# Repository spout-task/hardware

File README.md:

# SPOUT hardware

Hardware for a **SPOUT** rig, part of the [spout-task](https://github.com/spout-task) project.
Every device has its own folder with design files, pictures and a README that explains what it does,
what to buy, how to make it and how to connect it to SPOUT.

A complete rig costs about **1,080 USD** (about 1,440 USD including a computer and screen).
The full bill of materials is in [`SPOUT_BOM.xlsx`](SPOUT_BOM.xlsx) and [`SPOUT_BOM.pdf`](SPOUT_BOM.pdf).

<p align="center"><em>A SPOUT rig seen from above: head restrained setup (left), motorized manipulator with the spouts (center), electronics with the Teensy breakout board (top), water reservoirs (top right) and the stepper motor driver box (right).</em></p>

## Devices

| Group | Device | What it does | How it is made | Folder |
|---|---|---|---|---|
| Electronics | Teensy breakout board | Carries the Teensy 4.1, drives the solenoids and brings out all inputs and outputs | PCB, 3D printed housing | [`teensy_breakout_board`](teensy_breakout_board/) |
| Electronics | Dual lick detector | Detects licks on one or two spouts with sub millisecond precision | PCB, 3D printed housing | [`dual_lick_detector`](dual_lick_detector/) |
| Electronics | Optogenetics power modulator | Turns a Teensy PWM signal into a 0 to 5 V analog command, so light power can be set per trial | Hand built circuit, 3D printed housing | [`optogenetics_power_modulator`](optogenetics_power_modulator/) |
| Head fixation | Head restrained setup | Headplates and holders for behavior and for two photon imaging | Laser cut titanium headplates, machined aluminium holders, ramps and cone | [`head-restrained_setup`](head-restrained_setup/) |
| Head fixation | Breadboards | Rig base plate and round base for the head fixation | Machined aluminium by a machine shop (or bought) | [`breadboards`](breadboards/) |
| Spout positioning | Motorized manipulator | Three axis stepper stage that positions the spouts | Bought stages and drivers, 3D printed adapters, laser cut driver box and drilling templates | [`motorized_manipulator`](motorized_manipulator/) |
| Spout positioning | Spout holder | Holds the stainless steel lick spout(s) and the two solenoid valves | 3D printed spout holders, laser cut solenoid holder | [`spout_holder`](spout_holder/) |
| Miscellaneous | Housings | Boxes for the audio amplifier and for the power distribution breadboard | 3D printed | [`housing_miscellaneous`](housing_miscellaneous/) |

## Build order for one rig

1. **Base.** The 12 x 18 inch breadboard is the base of the rig.
2. **Head fixation.** Build the head restrained setup on the round breadboard: magnetic base, post, clamp, aluminium tube and headplate holders.
3. **Water delivery.** Reservoir syringes, 3 way valves, solenoids in the solenoid holder, Tygon tubing, and the spouts in the spout holder.
4. **Spout positioning.** Stack the three linear stages with the printed adapters, mount the spout holder on a post on the top stage, and put the three drivers in the laser cut box.
5. **Electronics.** Teensy breakout board in its housing, power distribution box, dual lick detector in its housing. Connect the spouts to the lick detector and ground the mouse through the aluminium tube.
6. **Sound.** Audio amplifier in its housing and two speakers on short posts.
7. **Optogenetics (optional).** Optogenetics power modulator between the Teensy and the LED or AOM driver.
8. **Software.** Flash the firmware and open the GUI, see the [software](https://github.com/spout-task/software) repository.

Photos of the build process will be added.

## Conventions

* 3D printed parts: Prusa MK3, PLA, standard settings.
* Screws: 1/4 20 for the breadboards and posts, 4-40 for small parts.
* Units: mm, except the breadboard STEP files (inch). DXF files are in mm.
* Each device folder has a `design` folder with `files` (design files) and `pictures` (renders). Electronics also have a `PCB` or `circuit` folder, and the manipulator a `schematics` folder.
* File types: STL to 3D print, DXF to laser cut, STEP to edit in CAD or to send to a machine shop. Flat parts come as DXF and STL, so you can laser cut or print them.
* Each README lists for every part how we made it and from what material.

## Related repositories
[software](https://github.com/spout-task/software), [analyses](https://github.com/spout-task/analyses), [settings](https://github.com/spout-task/settings), [example_data](https://github.com/spout-task/example_data)

## License
All hardware designs in this repository are released under **CERN-OHL-S-2.0** ([`LICENSE`](LICENSE)).
The dual lick detector and the Teensy breakout board were designed by the
[HMS Research Instrumentation Core](https://github.com/HMS-RIC), whose members are authors of SPOUT,
and are shared here as part of SPOUT. Newer revisions are developed in the HMS RIC repositories for the
[lick detector](https://github.com/HMS-RIC/2-Channel-Lick-Detector) and the
[Teensy breakout board](https://github.com/HMS-RIC/Teensy-Breakout-general-purpose).

## How to cite
See [`CITATION.cff`](CITATION.cff) and the [project overview](https://github.com/spout-task).

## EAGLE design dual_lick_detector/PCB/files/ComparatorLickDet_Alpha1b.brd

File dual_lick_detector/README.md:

# Dual lick detector

Two channel lick detector for head restrained mice. Each lick closes a tiny current path between the
spout and the grounded mouse; the detector turns that into a clean digital pulse for the Teensy, with
sub millisecond precision.

## At a glance

| | |
|---|---|
| Function | Detects licks on one or two spouts |
| Design | HMS Research Instrumentation Core, revision Alpha1e (KiCad 10) |
| Fabrication | PCB with commercial assembly, 3D printed housing |
| Approximate cost | 100 USD for the assembled board |
| Used by | SPOUT1 (one channel) and SPOUT2 (two channels) |

## Key features

* Battery powered, optically isolated front end.
* Adjustable threshold and (optionally) adjustable hysteresis (100 mV default).
* Multi turn potentiometers for fine adjustment; can be fitted with a scale dial.
* Selectable conduction mode or junction potential mode. SPOUT uses conduction mode.
* Power from micro USB or a barrel jack adapter.
* Indicator LEDs for power and lick detection; ESD protected front end.
* Optional input protection diodes to support shock delivery.

## How it works in SPOUT

In conduction mode each spout is pulled up to 9 V (from a 9 V battery) through a 4.7 MOhm resistor.
When the grounded mouse touches the spout, the voltage drops and a comparator switches. The input is
filtered with a 10 us RC filter and the comparator has 100 mV hysteresis. An optically isolated output
stage, powered by a separate 3 V adapter, drives the output through a 50 Ohm source termination, so the
signal can run over BNC cables. In the SPOUT configuration the output is active low.

## Files

| File | What it is |
|---|---|
| [`PCB/files/dual_lick_detector_.kicad_sch`](PCB/files/dual_lick_detector_.kicad_sch) | Schematic (KiCad 10) |
| [`PCB/files/dual_lick_detector_.kicad_pcb`](PCB/files/dual_lick_detector_.kicad_pcb) | Board layout (KiCad 10) |
| [`ComparatorLickDet_BOM.pdf`](ComparatorLickDet_BOM.pdf) | Component list, readable version (made for revision Alpha1d) |
| [`PCB/pictures`](PCB/pictures/) | Photos and board renders, see below |

| Part | Files | What it is | How we made it |
|---|---|---|---|
| Housing | [`.stl`](design/files/box_dual_lick_detector.stl), [`.step`](design/files/box_dual_lick_detector.step) | Housing, 152 x 89 x 20 mm, with mounting ears | 3D printed, PLA |

The SPOUT paper used revision Alpha1d (EAGLE). Alpha1e is the KiCad version of that design.
Newer revisions are developed in the [HMS RIC repository](https://github.com/HMS-RIC/2-Channel-Lick-Detector).

### Pictures

| Picture | What it shows |
|---|---|
| [`dual_lick_detector_1.jpg`](PCB/pictures/dual_lick_detector_1.jpg) | Assembled board with BNC connectors, potentiometers and battery holder |
| [`dual_lick_detector_2.jpg`](PCB/pictures/dual_lick_detector_2.jpg) | Bare board, top |
| [`dual_lick_detector_3.jpg`](PCB/pictures/dual_lick_detector_3.jpg) | Bare board, bottom |
| [`dual_lick_detector_schematic_1.png`](PCB/pictures/dual_lick_detector_schematic_1.png) | Board render from KiCad, bottom |
| [`dual_lick_detector_schematic_2.png`](PCB/pictures/dual_lick_detector_schematic_2.png) | Board render from KiCad, top |

## Bill of materials

| Qty | Part | Supplier | Part number | Price (USD) |
|---|---|---|---|---|
| 1 | Assembled lick detector board | Any PCB assembler (we used PCBWay) | KiCad files | 100 |
| 1 | 3D printed housing | | | |
| 1 | 9 V battery | | | |
| 1 | Power adapter 3 V (output stage) | NC | BY0301&BK | 5.57 |
| 1 | Stainless steel tube for the spouts | McMaster-Carr | 5560K72 | 3.90 |
| 1 | Banana socket and plug (mouse ground) | | | 2.98 |

Full list: [`SPOUT_BOM.xlsx`](../SPOUT_BOM.xlsx).

## Ordering the PCB

The board is designed in KiCad 10. Open the `.kicad_pcb` file in KiCad (free, [kicad.org](https://www.kicad.org)) and export
what your fabricator needs: Gerber and drill files (File, Fabrication Outputs), and for commercial assembly the
component list and the position file from the same menu. Default manufacturing settings are fine.

## Fabrication

1. Order the assembled board as described above. All the fine soldering will be done, you only need to solder big components on the PCB. The SPOUT boards were made and assembled by PCBWay.
2. On both sides of the PCB, solder dual jack BNC connectors in place.
3. On the top side of the PCB, you will have to solder two multi-turn potentiometers in place.
4. On the bottom side of the PCB, a DC barrel jack power connector (3V to send TTL to Teensy) and/or micro USB connector (5V if you want to send a TTL to an Arduino), a two-way toggle switch, and a 9V battery casing should be soldered in place.
5. Print `box_dual_lick_detector.stl` on a Prusa MK3 in PLA with standard settings. Mount the board with 4-40 screws and the housing on the breadboard with 1/4 20 screws.

## Assembly

1. Mount the board in the housing and the housing on the breadboard.
2. Connect the spouts to the inputs, and the outputs to the Teensy breakout board, as listed below.
3. Ground the mouse: connect the detector ground to the aluminium tube of the head restrained setup with the banana plug and socket.
4. Insert the 9 V battery and connect the 3 V adapter.
5. For imaging, split the lick outputs with a BNC T connector to your DAQ as well.

## Connections

Seen from the top, with the potentiometers facing up. Each side has two BNC connectors, one above the other.

| Part | SPOUT2 (two spouts) | SPOUT1 (one spout) |
|---|---|---|
| Left BNC, top | Left lick output, to PIN14_A0 on the Teensy breakout board | Lick output, to PIN14_A0 |
| Left BNC, bottom | Right lick output, to PIN41_A17 | Not used |
| Right BNC, top | Left lick input, from the left spout | Lick input, from the spout |
| Right BNC, bottom | Right lick input, from the right spout | Not used |
| Bottom LED | Left lick detected | Lick detected |
| Top LED | Right lick detected | Not used |
| Left potentiometer | Left lick threshold | Lick threshold |
| Right potentiometer | Right lick threshold | Not used |

## Testing and calibration

1. Touch a spout with one hand while touching the ground (aluminium tube) with the other: the lick LED lights up and the GUI shows the lick.
2. Set the threshold with the multi turn potentiometer (left for the left spout, right for the right spout) so a touch is detected reliably while the idle spout stays silent. Set it per rig, because cable length and grounding differ.

## License and attribution
Designed and developed by the [HMS Research Instrumentation Core](https://github.com/HMS-RIC), whose
members are authors of SPOUT, and shared here as part of SPOUT under **CERN-OHL-S-2.0**
([`LICENSE`](../LICENSE)). Newer revisions are developed in the
[HMS RIC repository](https://github.com/HMS-RIC/2-Channel-Lick-Detector).

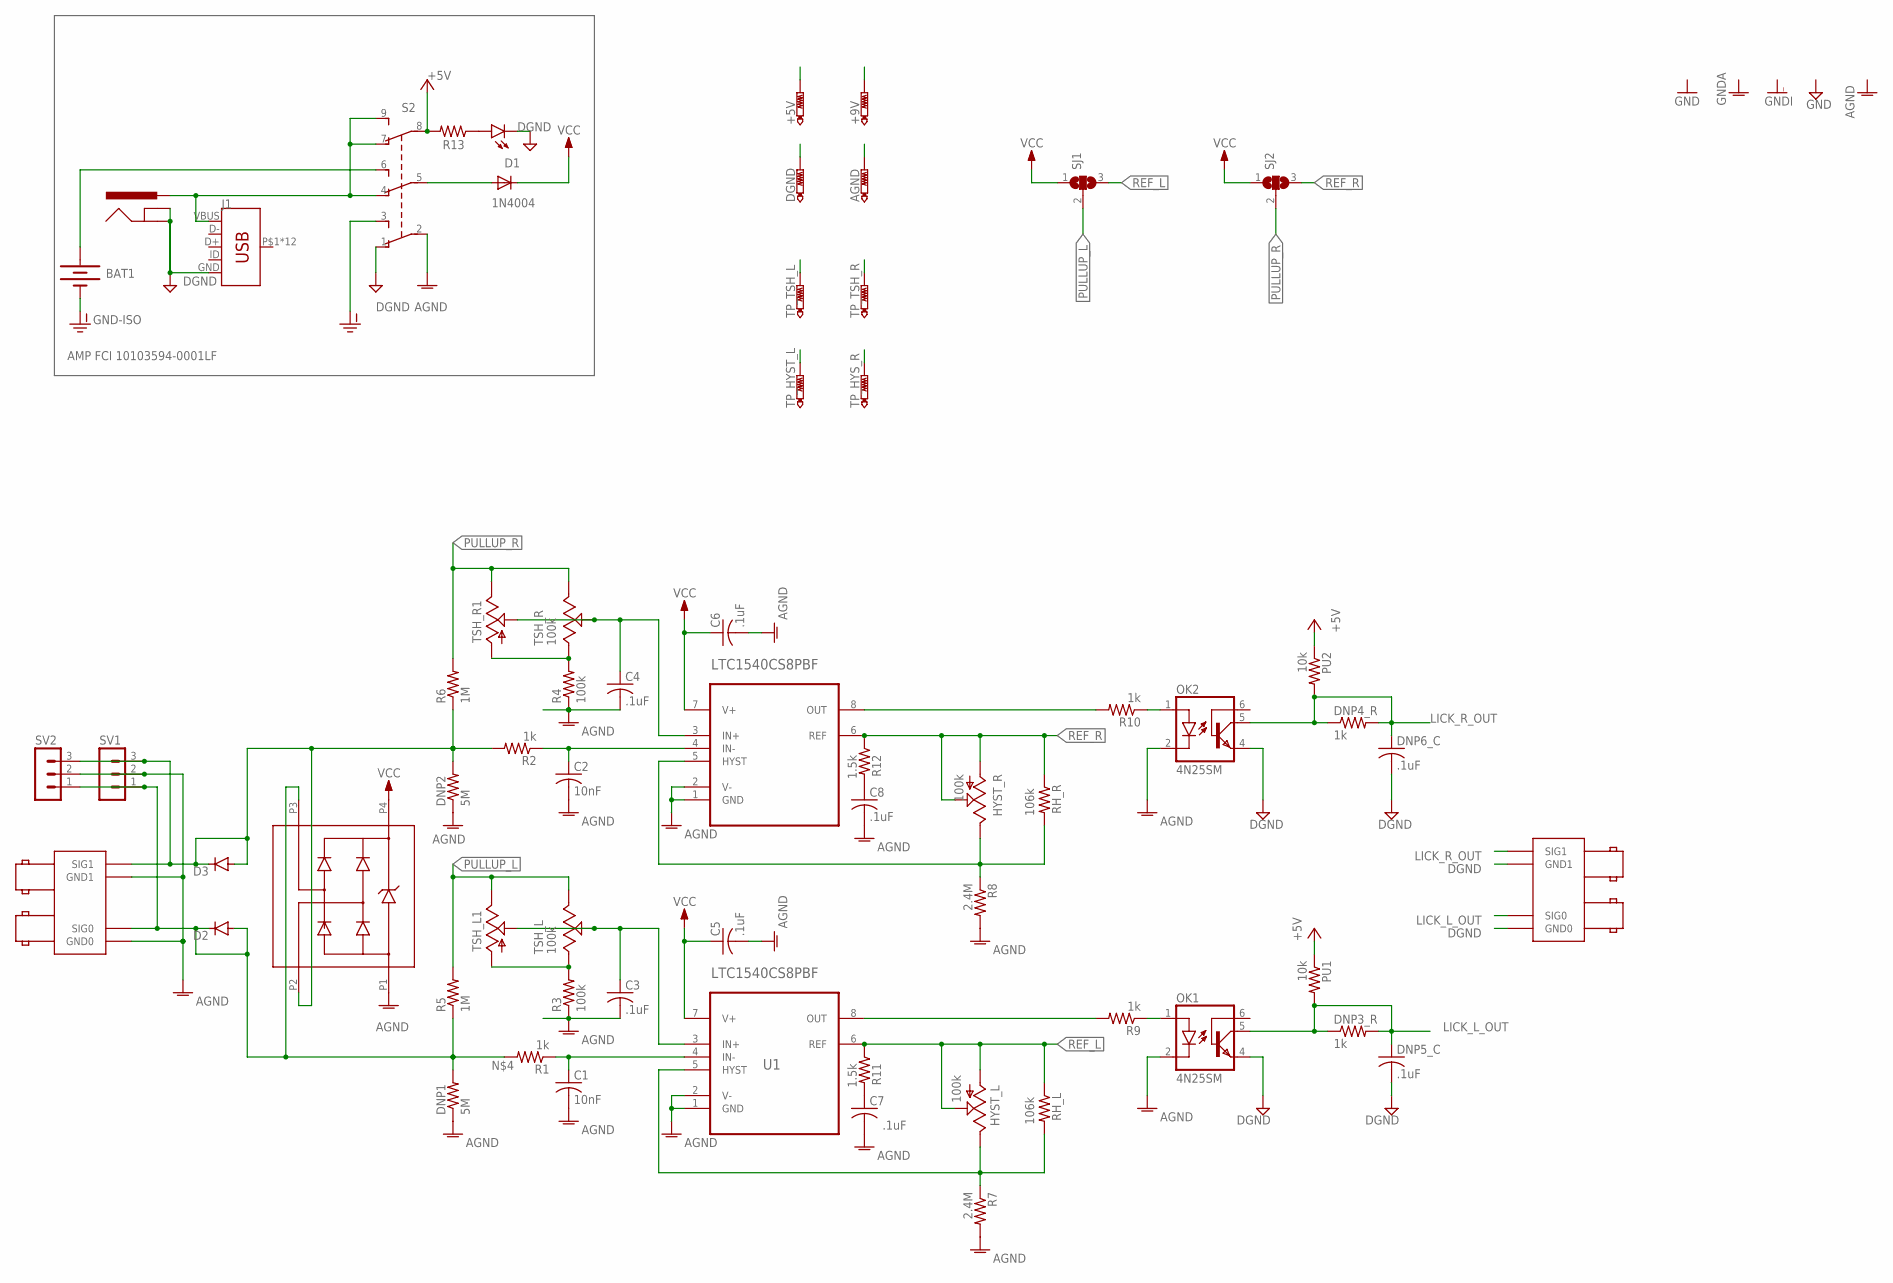
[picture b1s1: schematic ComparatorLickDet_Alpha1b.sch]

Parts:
+5V, +9V: PTR1PAD1-13Y; P1-13Y
AGND: PTR1PAD1-13Y; P1-13Y
BAT1: BATTERY9V; BATTCON_9V
C1, C2: 10nF; C0805
C3, C4, C5, C6, C7, C8: .1uF; C0805
D1: 1N4004; DO41-10
D2, D3: DIODE-D-2.5; D-2.5
DGND: PTR1PAD1-13Y; P1-13Y
DNP1, DNP2: 5M; M0805
DNP3_R, DNP4_R: 1k; M0805
DNP5_C, DNP6_C: .1uF; C0805
HYST_L: 100k; B25P
HYST_R: 100k; B25P
J1: AMP FCI 10103594-0001LF; USB-MICROB-PTH
JP10: POWER_JACKPTH_BREAD; POWER_JACK_PTH_BREAD
LICKS_IN: BNC_RIGHT_ANGLE_DOUBLE
LICKS_OUT: BNC_RIGHT_ANGLE_DOUBLE
OK1, OK2: 4N25SM; DIL6-SMD
PU1, PU2: 10k; M0805
PWR: LED3MM
R1, R2, R9, R10: 1k; M0805
R3, R4: 100k; M0805
R5, R6: 1M; M0805
R7, R8: 2.4M; M0805
R11, R12: 1.5k; M0805
R13: 330; R0805
RH_L: 106k; M0805
RH_R: 106k; M0805
S2: SWITCH-3PDT-TH-V; NKK-M20-9PIN-VERTICAL
SJ1, SJ2: SJ2W; SJ_2
SV1, SV2: MA03-1
TP_HYST_L: PTR1PAD1-13; P1-13
TP_HYS_R: PTR1PAD1-13; P1-13
TP_TSH_L: PTR1PAD1-13; P1-13
TP_TSH_R: PTR1PAD1-13; P1-13
TSH_L: 100k; TRIM_3590S-2-103L
TSH_L1: 100k; B25P
TSH_R: 100k; TRIM_3590S-2-103L
TSH_R1: 100k; B25P
U1, U2: LTC1540CS8PBF; SOIC127P600X175-8N
U3: CD143A-12_TVS; SOT-143

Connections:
+5V: +5V.TP, PU1.1, PU2.1, R13.2, S2.8 (P3)
+9V: +9V.TP, BAT1.+, S2.6 (S2)
AGND: AGND.TP, C1.2, C2.2, C3.2, C4.2, C5.2, C6.2, C7.2, C8.2, DNP1.1, DNP2.1, LICKS_IN.P$GND0 (GND0), LICKS_IN.P$GND1 (GND1), OK1.2 (C), OK2.2 (C), R3.1, R4.1, R7.2, R8.2, S2.2 (P1), SV1.2, SV2.2, U1.1 (GND), U1.2 (V-), U2.1 (GND), U2.2 (V-), U3.P1
DGND: DGND.TP, DNP5_C.2, DNP6_C.2, J1.GND, JP10.GND, JP10.GNDBREAK, LICKS_OUT.P$GND0 (GND0), LICKS_OUT.P$GND1 (GND1), OK1.4 (EMI), OK2.4 (EMI), PWR.K (C), S2.1 (O1)
GND-ISO: BAT1.-, S2.3 (S1)
HYST_L: HYST_L.E, R7.1, RH_L.2, TP_HYST_L.TP, U1.5 (HYST)
HYST_R: HYST_R.E, R8.1, RH_R.2, TP_HYS_R.TP, U2.5 (HYST)
LICK_L_IN: C1.1, R1.1, U1.4 (IN-)
LICK_L_OUT: DNP3_R.1, DNP3_R.2, DNP5_C.1, LICKS_OUT.P$SIG0 (SIG0), OK1.5 (COL), PU1.2
LICK_R_OUT: DNP4_R.1, DNP4_R.2, DNP6_C.1, LICKS_OUT.P$SIG1 (SIG1), OK2.5 (COL), PU2.2
unnamed: R3.2, TSH_L.1 (CCW), TSH_L1.A
unnamed: D2.A, D2.C, DNP1.2, LICKS_IN.P$SIG0 (SIG0), R1.2, R5.1, SV1.1, SV2.1, U3.P3
unnamed: J1.VBUS, JP10.PWR, S2.4 (O2), S2.7 (O3), S2.9 (S3)
unnamed: C7.1, R11.2
unnamed: R4.2, TSH_R.1 (CCW), TSH_R1.A
unnamed: C2.1, R2.1, U2.4 (IN-)
unnamed: C8.1, R12.2
unnamed: D3.A, D3.C, DNP2.2, LICKS_IN.P$SIG1 (SIG1), R2.2, R6.1, SV1.3, SV2.3, U3.P2
unnamed: PWR.A, R13.1
unnamed: OK1.1 (A), R9.1
unnamed: R9.2, U1.8 (OUT)
unnamed: OK2.1 (A), R10.1
unnamed: R10.2, U2.8 (OUT)
PULLUP_L: R5.2, SJ1.2, TSH_L.3 (CW), TSH_L1.E
PULLUP_R: R6.2, SJ2.2, TSH_R.3 (CW), TSH_R1.E
REF_L: HYST_L.A, HYST_L.S, R11.1, RH_L.1, SJ1.3, U1.6 (REF)
REF_R: HYST_R.A, HYST_R.S, R12.1, RH_R.1, SJ2.3, U2.6 (REF)
TSH_L: C3.1, TP_TSH_L.TP, TSH_L.2 (WIPER), TSH_L1.S, U1.3 (IN+)
TSH_R: C4.1, TP_TSH_R.TP, TSH_R.2 (WIPER), TSH_R1.S, U2.3 (IN+)
VCC: C5.1, C6.1, D1.C, SJ1.1, SJ2.1, U1.7 (V+), U2.7 (V+), U3.P4
VIN: D1.A, S2.5 (P2)

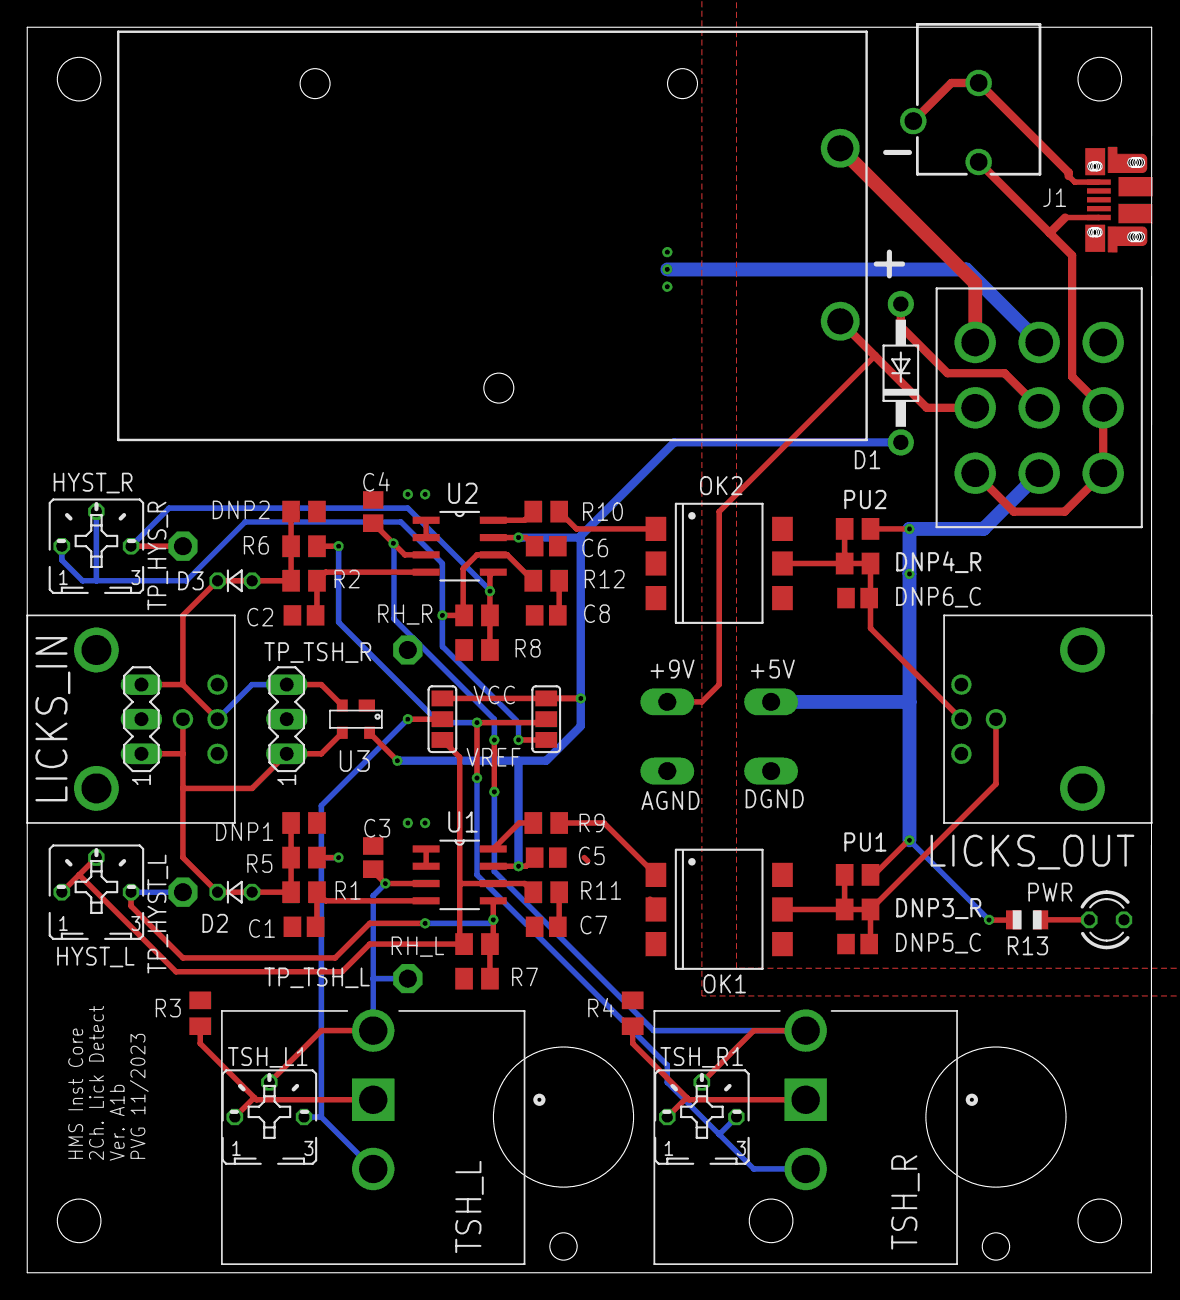
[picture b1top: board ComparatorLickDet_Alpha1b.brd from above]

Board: 2 copper layers, 82.5 x 91.4 mm, 64 parts (0 on the bottom side), 31 nets.

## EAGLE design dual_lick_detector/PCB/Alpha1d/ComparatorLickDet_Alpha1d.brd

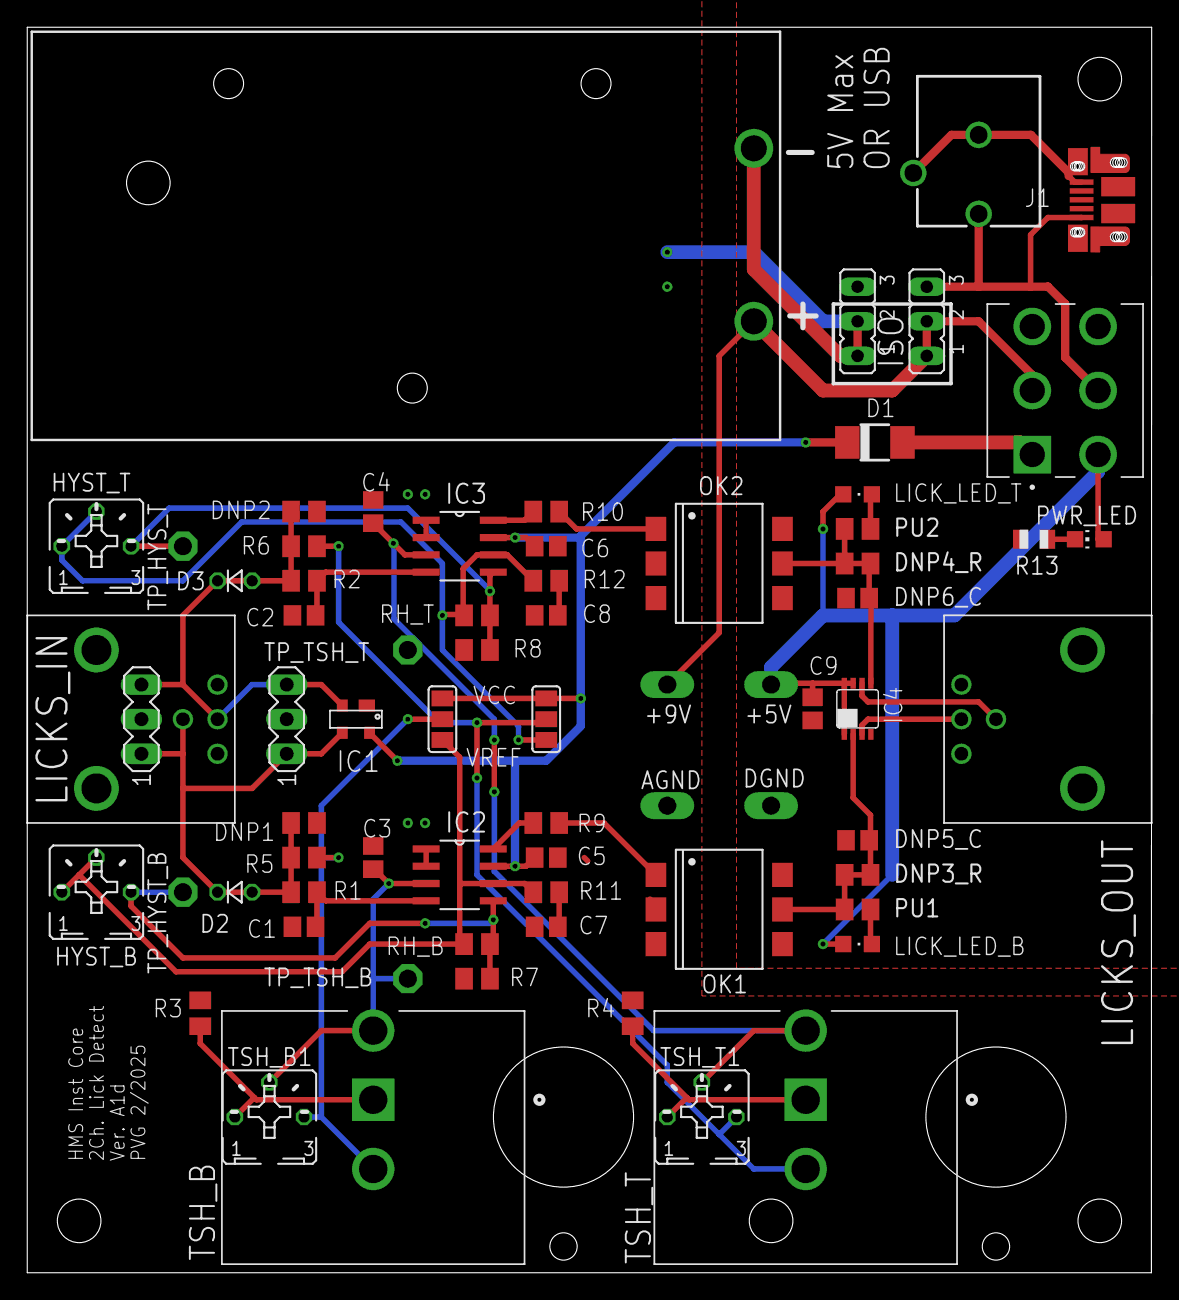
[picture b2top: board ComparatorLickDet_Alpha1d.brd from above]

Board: 2 copper layers, 82.5 x 91.4 mm, 70 parts (0 on the bottom side), 34 nets.

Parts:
+5V, +9V: PTR1PAD1-13Y; P1-13Y
AGND: PTR1PAD1-13Y; P1-13Y
BAT1: BATTCON_9V
C1, C2: 10nF; C0805
C3, C4, C5, C6, C7, C8, C9: .1uF; C0805
D1: DO-214AC
D2, D3: D-2.5
DGND: PTR1PAD1-13Y; P1-13Y
DNP1, DNP2: 5M; M0805
DNP3_R, DNP4_R: 1k; M0805
DNP5_C, DNP6_C: .1uF; C0805
HYST_B: 100k; B25P
HYST_T: 100k; B25P
IC1: CD143A-12_TVS; SOT-143
IC2, IC3: LTC1540CS8PBF; SOIC127P600X175-8N
IC4: SN74LVC2G126DCT; DCT_R-PDSO-G8
J1: AMP FCI 10103594-0001LF; USB-MICROB-PTH
JP1, JP2: JP2
JP10: POWER_JACKPTH_BREAD; POWER_JACK_PTH_BREAD
LICKS_IN: BNC_RIGHT_ANGLE_DOUBLE
LICKS_OUT: BNC_RIGHT_ANGLE_DOUBLE
LICK_LED_B: CHIPLED_0805
LICK_LED_T: CHIPLED_0805
OK1, OK2: 4N25SM; DIL6-SMD
PU1, PU2: 10k; M0805
PWR_LED: CHIP-LED0805
R1, R2, R9, R10: 1k; M0805
R3, R4: 51k; M0805
R5, R6: 4.7M; M0805
R7, R8: 2.4M; M0805
R11, R12: 1.5k; M0805
R13: 1k; R0805
RH_B: 100k; M0805
RH_T: 100k; M0805
S1: 500SDP1S1M2QEA; SW_500SDP1S1M2QEA
SJ1, SJ2: SJ_2
SV1, SV2: MA03-1
TP_HYST_B: PTR1PAD1-13; P1-13
TP_HYS_T: PTR1PAD1-13; P1-13
TP_TSH_B: PTR1PAD1-13; P1-13
TP_TSH_T: PTR1PAD1-13; P1-13
TSH_B: 100k; TRIM_3590S-2-103L
TSH_B1: 100k; B25P
TSH_T: 100k; TRIM_3590S-2-103L
TSH_T1: 100k; B25P

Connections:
+5V: +5V.TP, C9.1, IC4.1, IC4.7, IC4.8, LICK_LED_B.A, LICK_LED_T.A, PWR_LED.A, S1.4
+9V: +9V.TP, BAT1.+, JP1.1, JP1.2, S1.2
AGND: AGND.TP, BAT1.-, C1.2, C2.2, C3.2, C4.2, C5.2, C6.2, C7.2, C8.2, DNP1.1, DNP2.1, IC1.P1, IC2.1, IC2.2, IC3.1, IC3.2, JP2.1, JP2.2, LICKS_IN.P$GND0, LICKS_IN.P$GND1, OK1.2, OK2.2, R3.1, R4.1, R7.2, R8.2, SV1.2, SV2.2
DGND: C9.2, DGND.TP, DNP5_C.2, DNP6_C.2, IC4.4, J1.GND, JP2.3, JP10.GND, JP10.GNDBREAK, LICKS_OUT.P$GND0, LICKS_OUT.P$GND1, OK1.4, OK2.4, R13.1
HYST_B: HYST_B.E, IC2.5, R7.1, RH_B.2, TP_HYST_B.TP
HYST_T: HYST_T.E, IC3.5, R8.1, RH_T.2, TP_HYS_T.TP
LICK_B_OUT: IC4.6, LICKS_OUT.P$SIG0
LICK_L_IN: C1.1, IC2.4, R1.1
LICK_T_OUT: IC4.3, LICKS_OUT.P$SIG1
unnamed: R3.2, TSH_B.1, TSH_B1.A
unnamed: DNP3_R.1, DNP3_R.2, DNP5_C.1, IC4.2, OK1.5, PU1.2
unnamed: D2.A, D2.C, DNP1.2, IC1.P3, LICKS_IN.P$SIG0, R1.2, R5.1, SV1.1, SV2.1
unnamed: PWR_LED.C, R13.2
unnamed: D1.A, S1.1
unnamed: C7.1, R11.2
unnamed: R4.2, TSH_T.1, TSH_T1.A
unnamed: C2.1, IC3.4, R2.1
unnamed: C8.1, R12.2
unnamed: D3.A, D3.C, DNP2.2, IC1.P2, LICKS_IN.P$SIG1, R2.2, R6.1, SV1.3, SV2.3
unnamed: DNP4_R.1, DNP4_R.2, DNP6_C.1, IC4.5, OK2.5, PU2.2
unnamed: LICK_LED_B.C, PU1.1
unnamed: LICK_LED_T.C, PU2.1
unnamed: OK1.1, R9.1
unnamed: IC2.8, R9.2
unnamed: OK2.1, R10.1
unnamed: IC3.8, R10.2
PULLUP_B: R5.2, SJ1.2, TSH_B.3, TSH_B1.E
PULLUP_T: R6.2, SJ2.2, TSH_T.3, TSH_T1.E
REF_B: HYST_B.A, HYST_B.S, IC2.6, R11.1, RH_B.1, SJ1.3
REF_T: HYST_T.A, HYST_T.S, IC3.6, R12.1, RH_T.1, SJ2.3
TSH_B: C3.1, IC2.3, TP_TSH_B.TP, TSH_B.2, TSH_B1.S
TSH_T: C4.1, IC3.3, TP_TSH_T.TP, TSH_T.2, TSH_T1.S
VCC: C5.1, C6.1, D1.C, IC1.P4, IC2.7, IC3.7, SJ1.1, SJ2.1
VIN: J1.VBUS, JP1.3, JP10.PWR, S1.5

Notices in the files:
parts and their libraries:
SparkFun-Connectors: Licensing: Creative Commons ShareAlike 4.0 International - https://creativecommons.org/licenses/by-sa/4.0
